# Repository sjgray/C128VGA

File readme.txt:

Simple C128 to VGA 15kHz Adapter
================================

This is an adapter to convert the C128's 80-column RGBI output
to any VGA monitor that accepts 15kHz scan rate. It uses a
simple RGBI to RGB DAC and does not require any external power.
The adapter also has an RCA connector for Mono composite out.

Project Website
---------------

http://www.cbmsteve.ca/c128vga/index.html

Notes
-----

The DB9 and DE15 pcb-mount connectors both need the hex screws removed in order to connect.
Some cheap connectors will fall apart if the screws are removed. Find ones that are crimped properly.

Gerbers
-------

You can send the ZIP file to most board houses. I use JLCPCB and have had no issues.

History
-------

2024-07-16: V1.0 Prototype PCB with TRS design complete. Gerbers sent to JLCPCB.
2024-07-29: V1.1 Revised PCB with RCA connector complete. Gerbers sent to JLCPCB.
2024-08-07: V1.2 Fixed RCA footprint. Gerbers sent to JLCPCB.
2024-08-07: Webpage created. Uploaded files to GitHub.

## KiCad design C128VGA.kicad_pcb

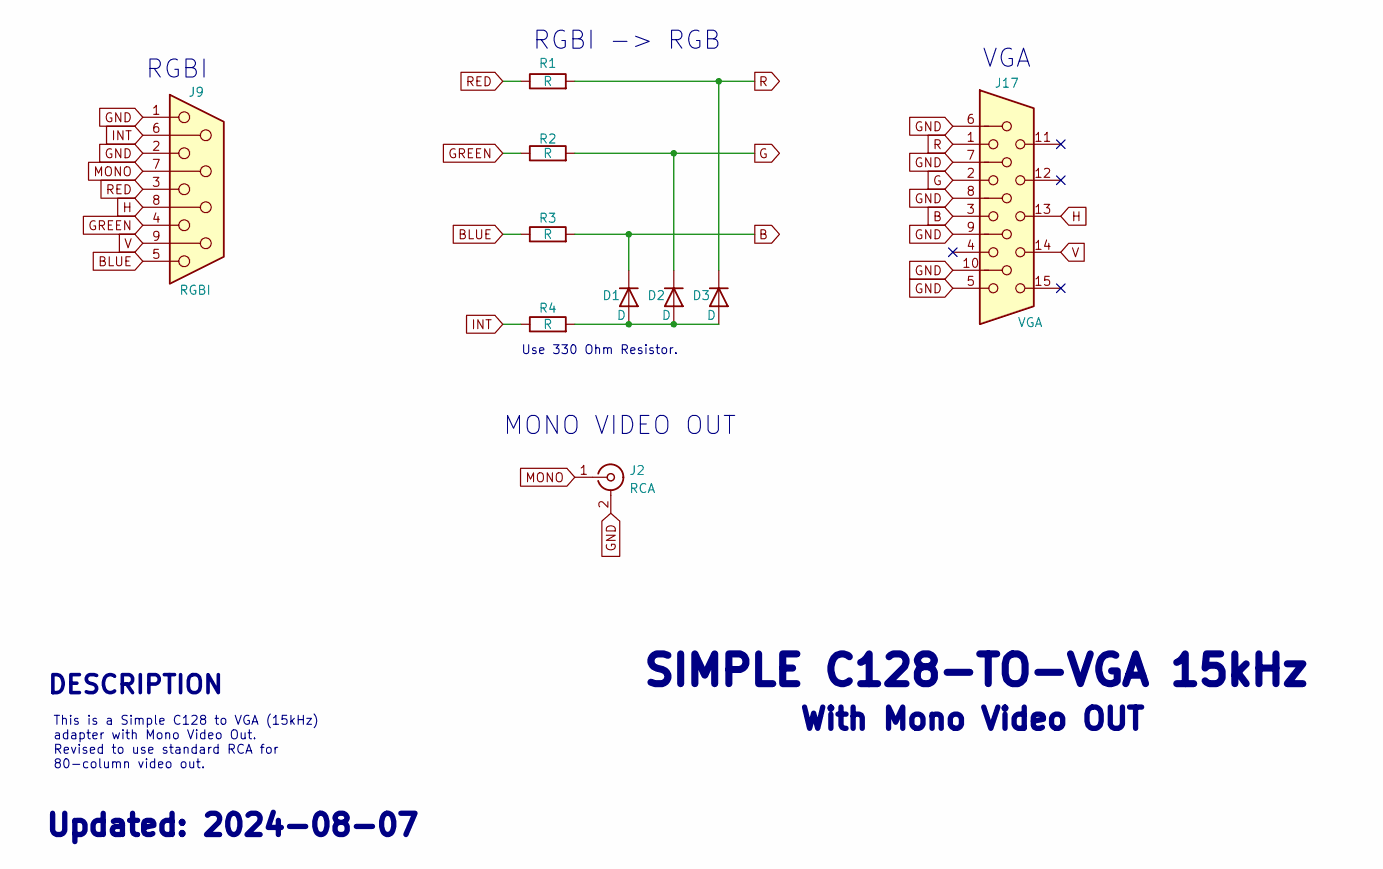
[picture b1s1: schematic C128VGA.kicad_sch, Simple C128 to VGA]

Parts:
D1, D2, D3: D; D_DO-35_SOD27_P7.62mm_Horizontal
J2: RCA; RCA-custom
J9: RGBI; DSUB-9_Male_Horizontal_P2.77x2.84mm_EdgePinOffset4.94mm_Hou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
J17: VGA; DSUB-15-HD_Female_Horizontal_P2.29x1.98mm_EdgePinOffset3.03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
R1, R2, R3, R4: R; R_Axial_DIN0204_L3.6mm_D1.6mm_P7.62mm_Horizontal

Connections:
B: D1.1 (K), J17.3, R3.2
BLUE: J9.5, R3.1
G: D2.1 (K), J17.2, R2.2
GND: J2.2 (Ext), J9.1, J9.2, J17.5, J17.6, J17.7, J17.8, J17.9, J17.10
GREEN: J9.4, R2.1
H: J9.8, J17.13
INT: J9.6, R4.1
MONO: J2.1 (In), J9.7
unnamed: D1.2 (A), D2.2 (A), D3.2 (A), R4.2
R: D3.1 (K), J17.1, R1.2
RED: J9.3, R1.1
V: J9.9, J17.14

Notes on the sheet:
MONO VIDEO OUT
Updated: 2024-08-07
RGBI
Use 330 Ohm Resistor.
RGBI -> RGB
With Mono Video OUT
DESCRIPTION
VGA
This is a Simple C128 to VGA (15kHz) adapter with Mono Video Out. Revised to use standard RCA for 80-column video out.
SIMPLE C128-TO-VGA 15kHz

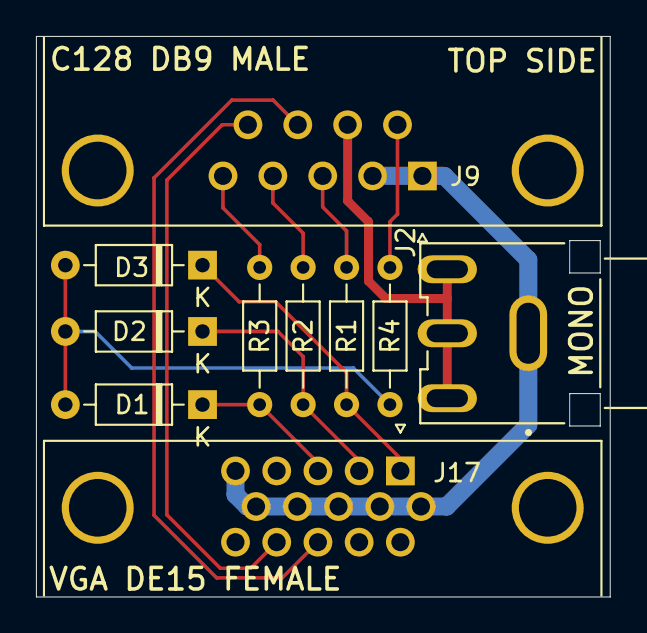
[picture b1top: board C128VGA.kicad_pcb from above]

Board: 2 copper layers, 31.9 x 31.1 mm, 10 parts (0 on the bottom side), 12 nets.

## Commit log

2024-08-07 V1.2
    Initial public release.
